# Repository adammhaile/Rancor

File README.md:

# Rancor 3D Printer

Rancor is a project that came about from being inspired by seeing all the awesome projects at MRRF 2021 and is my first ground-up 3D printer design. It is an IDEX machine with a "spared no expense" and "there's no such thing as too much feature creep" design philosophy. Learning to CNC machine aluminium with my new [MilkCr8 CNC](https://github.com/Makers-On-Tap/milkcr8-cnc) was also a major factor, so if a component *could* be machined out of 1/4" aluminum tooling plate, it was. It was never designed to be manufactured and mainly exists as somethingt to show off.

## Specs

- Cartesian IDEX motion system
- 45 parts custom machined from aluminum tooling plate
- Cold-swappable tools require only 3 bolts and a 14-pin Molex Mini-Fit connector
- 5 currently configured tools that can be used
    - 2x E3D Hemera & Revo
    - 3x E3D Hemera & copper block, Slice 50W heater, Bondtech CHT nozzle (1.0mm, 1.4mm, 1.8mm)
- 330x320x600 mm print volume
- Prusa SuperPINDA ABL probe
- 0.9° LDO 42STH60-2004MAC Motors for each axis
- LDO MGN12 Linear Rails
- PTFE coated LDO leadscrews for Z
- Mandala Rose Works 6.35mm MIC6 cast aluminum bed (Railcore)
- Mandala Rose Works Z axis bed yokes (Railcore)
- Mandala Rose Works Z Oldham Wobblers (Railcore)
- 750W 120V AC Keenovo Bed Heater
- Duet 6HC mainboard with Duet 3HC expansion to drive all 9 motors
- 930x550x960 mm outter dimensions (excluding tool cables)
- 7.9" 400x1280 LCD display for g-code scrolling
- 13.3" 1080x1920 LCD touch display to show the Duet DWC interface
- 2x Raspberry Pi 4 - One for Duet SBC and one running Android for DWC display
- Filament sensors for each tool, based on the Prusa Mini sensor
- Internal network between the two Pi 4's using a Linksys router that provides on-site WiFi
- Ethernet connection for Duet SBC Pi for normal network connectivity
- Teensy 3.2 managed "voice" output controlled via a Duet UART connection

## CAD

All of the CAD for this project was done in Fusion 360 and the files (both F360 and STEP) can be found on [this release page](https://github.com/adammhaile/Rancor/releases/tag/cad_release).

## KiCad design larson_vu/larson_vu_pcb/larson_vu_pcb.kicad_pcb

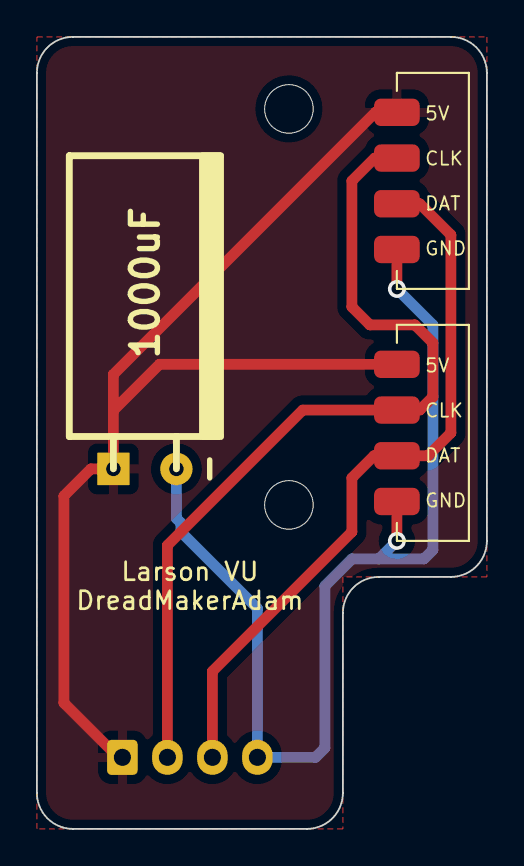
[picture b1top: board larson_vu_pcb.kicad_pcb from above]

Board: 2 copper layers, 25.0 x 44.0 mm, 6 parts (1 on the bottom side), 4 nets.

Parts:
C1: 1000uF; CP_8x15mm_horiz-L
H1, H2: MountingHole; MountingHole_2.7mm_M2.5
J1: FromController; JST_XH_B4B-XH-A_1x04_P2.50mm_Vertical
J2, J3: ToStrip; APA102_STRIP

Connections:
5V: C1.1, J1.1, J2.1, J3.1
CLK: J1.2, J2.2, J3.2
DATA: J1.3, J2.3, J3.3
GND: C1.2, J1.4, J2.4, J3.4

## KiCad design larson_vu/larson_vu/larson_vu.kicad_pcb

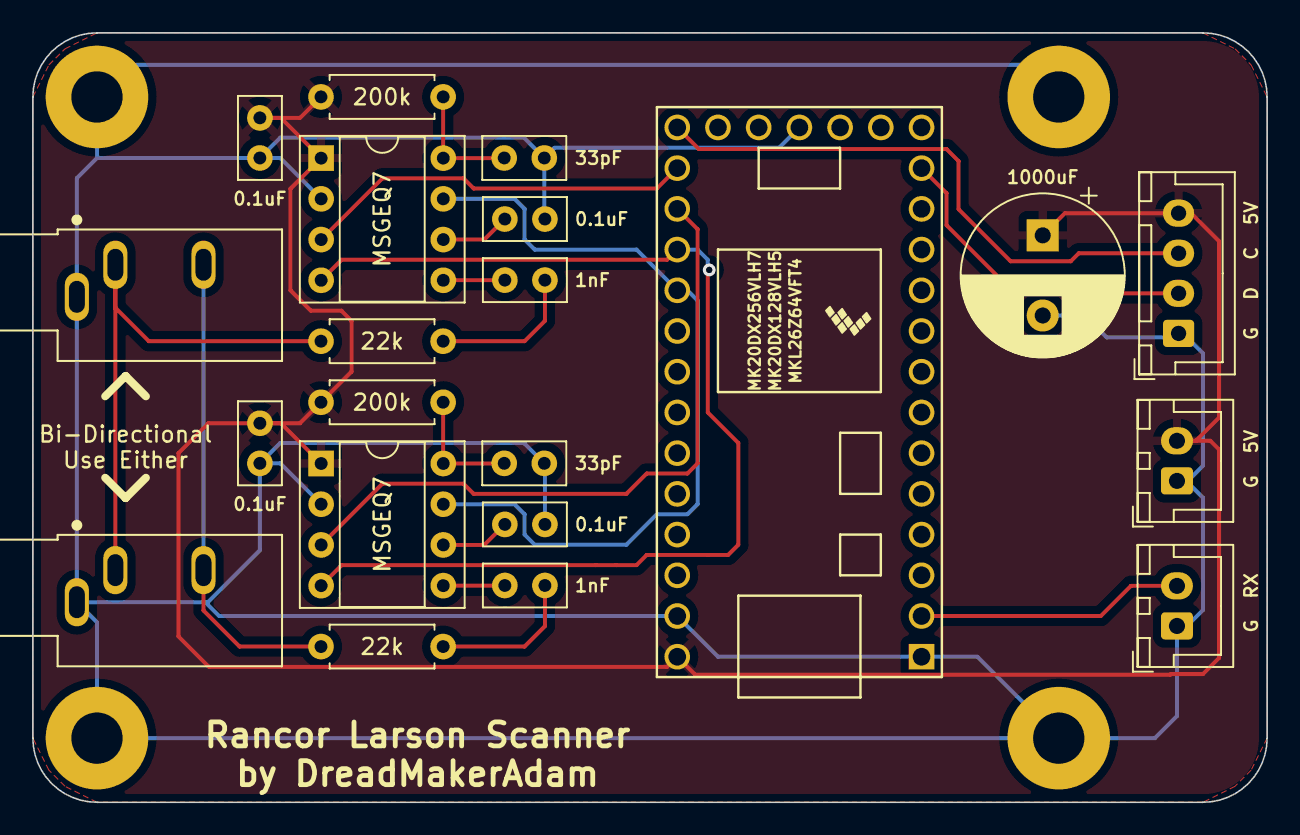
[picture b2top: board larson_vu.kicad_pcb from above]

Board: 2 copper layers, 77.0 x 48.0 mm, 25 parts (0 on the bottom side), 19 nets.

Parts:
A1, A2: SJ1-3533NG; CUI_SJ1-3533NG
C1, C2, C7, C8: 0.1uF; C_Disc_D5.0mm_W2.5mm_P2.50mm
C3, C4: 1nF; C_Disc_D5.0mm_W2.5mm_P2.50mm
C5, C6: 33pF; C_Disc_D5.0mm_W2.5mm_P2.50mm
C9: 1000uF; CP_Radial_D10.0mm_P5.00mm
H1, H2, H3, H4: MountHole; MountingHole_3.2mm_M3_Pad
J1: Power; JST_XH_B2B-XH-A_1x02_P2.50mm_Vertical
J2: UART; JST_XH_B2B-XH-A_1x02_P2.50mm_Vertical
J3: LED_OUT; JST_XH_B4B-XH-A_1x04_P2.50mm_Vertical
R1, R2: 22k; R_Axial_DIN0207_L6.3mm_D2.5mm_P7.62mm_Horizontal
R3, R4: 200k; R_Axial_DIN0207_L6.3mm_D2.5mm_P7.62mm_Horizontal
U1: Teensy3.2; Teensy30_31_32_LC
U2, U3: MSGEQ7; DIP-8_W7.62mm_Socket

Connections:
+5V: C1.2, C2.2, C9.1, J1.2, J3.4, R3.1, R4.1, U1.33 (Vin), U2.1 (VDD), U3.1 (VDD)
A0: U1.21 (14_A0_SCK), U2.3 (OUT)
A1: U1.22 (15_A1_CS_Touch), U3.3 (OUT)
AUDIO_L: A1.2, A2.2, R1.1
AUDIO_R: A1.3, A2.3, R2.1
GND: A1.1, A2.1, C1.1, C2.1, C5.2, C6.2, C7.1, C8.1, C9.2, H1.1, H2.1, H3.1, H4.1, J1.1, J2.1, J3.1, U1.1 (GND), U1.17 (GND), U1.32 (AGND), U2.2 (VSS), U3.2 (VSS)
LED_CLOCK: J3.3, U1.20 (13_LED_SCK)
LED_DATA: J3.2, U1.13 (11_DOUT)
unnamed: C3.1, R1.2
unnamed: C3.2, U2.5 (IN)
unnamed: C4.1, R2.2
unnamed: C4.2, U3.5 (IN)
unnamed: C5.1, R3.2, U2.8 (CKIN)
unnamed: C6.1, R4.2, U3.8 (CKIN)
unnamed: C7.2, U2.6 (GND)
unnamed: C8.2, U3.6 (GND)
RESET: U1.24 (17_A3_SDA0_Touch), U2.7 (RESET), U3.7 (RESET)
RX: J2.2, U1.2 (0_RX1_Touch)
STROBE: U1.23 (16_A2_SCL0_Touch), U2.4 (STROBE), U3.4 (STROBE)

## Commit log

2022-02-20 Initial gcode scroller
2022-02-20 mostly working gcode scroller
2022-02-20 minor tweaks to scroller
2022-02-20 add sd sync
2022-02-20 Add audio files/firmware
2022-02-22 Add more sound options
2022-03-03 update scroller
2022-03-03 update sync
2022-03-06 Basic voice gen script
2022-03-06 Update phrases
2022-03-11 Functional motion config
2022-03-11 Add startup level
2022-03-12 ignore last phrase file
2022-03-12 Add audio SD content
2022-03-13 Make gcode scroller keep running if DSF restarts
2022-03-13 variable-ize the shit out of everything
2022-03-14 Add random audio handling in arduino
2022-03-14 Correctly handle ctrl+c in gcode scroller
2022-03-14 update sync to re-own files
2022-03-16 config backup
2022-03-16 Add new phrases
2022-03-18 sd backup
2022-03-18 wipe/purge routines
2022-03-19 filament management and dynamic tools
2022-03-19 Tweaks to filament handling
2022-03-19 Add park macro
2022-03-31 Audio export now mono
2022-03-31 Added larson scanner PCB
2022-04-01 better tool and filament handling
2022-04-01 Starting on larson
2022-04-04 Add automated tool provisioning
2022-04-05 config update
2022-04-07 VU firmware for Uno
2022-04-07 new LED strip board
2022-04-08 larson_vu switch between larson and audio
2022-04-14 add push sd script
2022-04-23 Allow setting anim type and mode
2022-04-23 Tweak VU firmware
2022-04-23 update vu firmware for final install
2022-04-29 Backup from failed SD
2022-04-29 tweak gcode scroller run
2022-05-05 Update offsets
2022-05-10 backup
2022-05-11 Added more phrases
2022-05-15 Bed and prime config system
2022-05-15 Set prime for all
2022-05-15 Cleanup SD content
2022-05-15 Fix audio randomness
2022-05-18 Add sound macros
2022-05-18 Add slicer config
2022-05-18 fix macro
2022-05-22 Adding calibration test files
2022-05-26 ignore csv files
2022-05-26 Add gcode scroller boot sequence
2022-05-26 Add README
2022-06-04 Add direct timelapse control from journal polling
2022-06-05 sys sync
2022-06-05 slicer backup
2022-06-06 Fix timing for final video record
2022-06-16 Slicer update
2022-06-18 PS Backup
2022-06-18 Add CAD file release info
2022-10-15 Add 0.6 nozzle configs
